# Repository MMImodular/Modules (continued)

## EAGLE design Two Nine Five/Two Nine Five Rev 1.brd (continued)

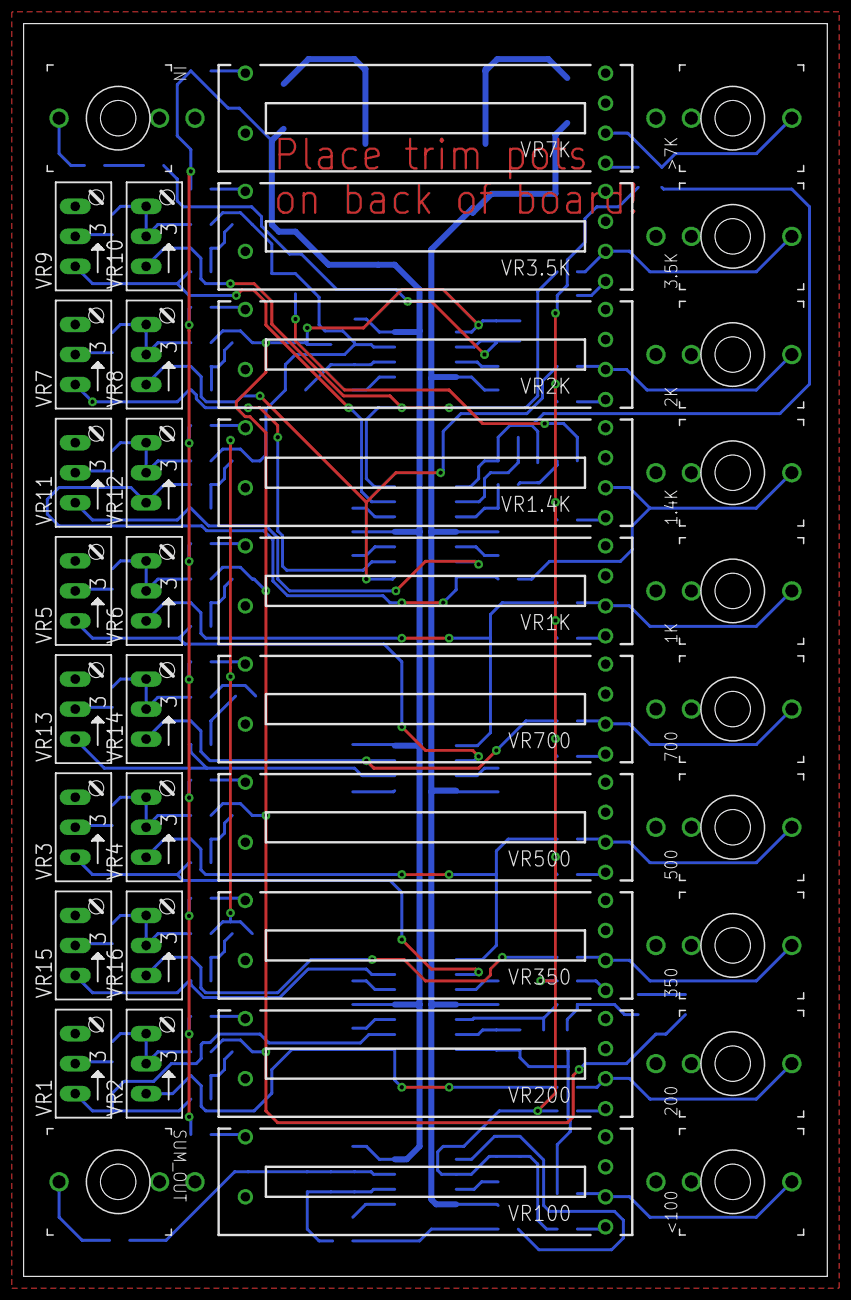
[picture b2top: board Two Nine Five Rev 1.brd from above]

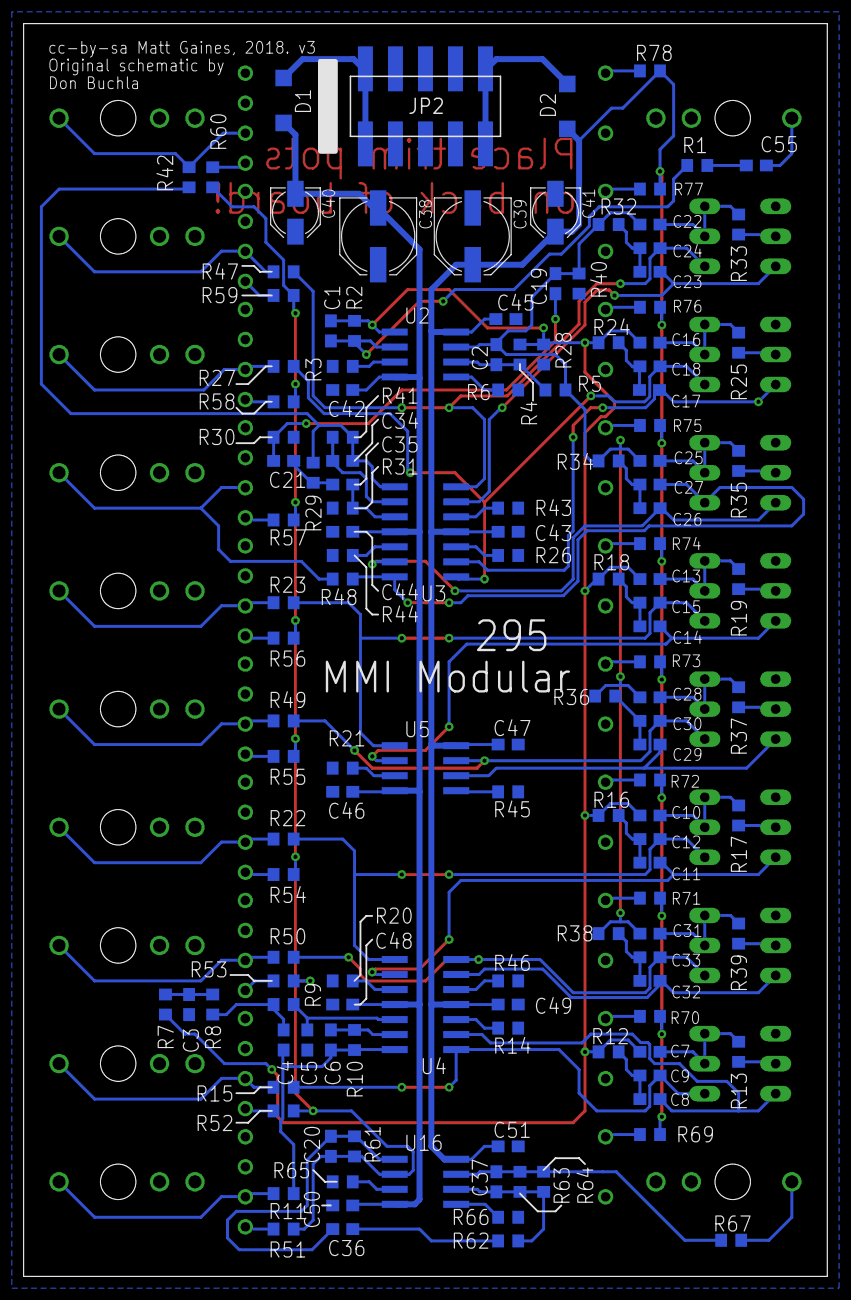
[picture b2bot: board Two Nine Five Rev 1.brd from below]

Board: 2 copper layers, 68.0 x 106.0 mm, 175 parts (137 on the bottom side), 109 nets.

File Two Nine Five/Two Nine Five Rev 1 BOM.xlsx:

Qty | Value | Device | Package | Parts | Description | SPICEPREFIX | Column1
1 |  | PINHD-2X5SMT | 2X05_SMT | JP2 | Surface mount pin header
2 | .0015uF | C-USC0603 | C0603 | C5, C29 | CAPACITOR, American symbol
6 | .0022uF | C-USC0603 | C0603 | C11, C19, C21, C22, C24, C35 | CAPACITOR, American symbol
5 | .0047uF | C-USC0603 | C0603 | C16, C18, C25, C27, C32 | CAPACITOR, American symbol
5 | .01uF | C-USC0603 | C0603 | C8, C13, C15, C28, C30 | CAPACITOR, American symbol
4 | .022uF | C-USC0603 | C0603 | C10, C12, C31, C33 | CAPACITOR, American symbol
3 | .047uF | C-USC0603 | C0603 | C3, C7, C9 | CAPACITOR, American symbol
1 | .22uF | C-USC0603 | C0603 | C4 | CAPACITOR, American symbol
1 | .47uF | C-USC0603 | C0603 | C55 | CAPACITOR, American symbol
1 | 0.47uF | C-USC0603 | C0603 | C36 | CAPACITOR, American symbol
1 | 1.5k | R-US_R0603 | R0603 | R29 | RESISTOR, American symbol
2 | 100k | R-US_R0603 | R0603 | R14, R43 | RESISTOR, American symbol
8 | 100k | TRIM_US-RJ9W | RJ9W | VR1, VR3, VR5, VR7, VR9, VR11, VR13, VR15 | 25-TURN TRIM POTENTIOMETER
10 | 100nF | C-USC0603 | C0603 | C42, C43, C44, C45, C46, C47, C48, C49, C50, C51 | CAPACITOR, American symbol
6 | 100pF | C-USC0603 | C0603 | C1, C2, C6, C20, C34, C37 | CAPACITOR, American symbol
10 | 10k | R-US_R0603 | R0603 | R69, R70, R71, R72, R73, R74, R75, R76, R77, R78 | RESISTOR, American symbol
2 | 10uF | CPOL-USB | PANASONIC_B | C40, C41 | POLARIZED CAPACITOR, American symbol | C
7 | 150k | R-US_R0603 | R0603 | R10, R19, R20, R25, R35, R37, R46 | RESISTOR, American symbol
9 | 15k | R-US_R0603 | R0603 | R6, R12, R16, R18, R24, R32, R34, R36, R38 | RESISTOR, American symbol
5 | 180k | R-US_R0603 | R0603 | R21, R26, R41, R44, R45 | RESISTOR, American symbol
2 | 1N5819 | DIODE-SOD123 | SOD123 | D1, D2 | DIODE
8 | 20k | TRIM_US-RJ9W | RJ9W | VR2, VR4, VR6, VR8, VR10, VR12, VR14, VR16 | POTENTIOMETER
11 | 220 | R-US_R0603 | R0603 | R11, R15, R22, R23, R27, R42, R47, R48, R49, R50, R67 | RESISTOR, American symbol
1 | 220k | R-US_R0603 | R0603 | R31 | RESISTOR, American symbol
2 | 330 | R-US_R0603 | R0603 | R28, R40 | RESISTOR, American symbol
16 | 33k | R-US_R0603 | R0603 | R1, R2, R3, R4, R5, R51, R53, R54, R55, R56, R57, R59, R60, R62, R63, R66 | RESISTOR, American symbol
2 | 39k | R-US_R0603 | R0603 | R52, R58 | RESISTOR, American symbol
1 | 4.7k | R-US_R0603 | R0603 | R65 | RESISTOR, American symbol
2 | 470pF | C-USC0603 | C0603 | C17, C23 | CAPACITOR, American symbol
2 | 47uF | CPOL-USD | PANASONIC_D | C38, C39 | POLARIZED CAPACITOR, American symbol | C
4 | 56k | R-US_R0603 | R0603 | R7, R8, R9, R61 | RESISTOR, American symbol
1 | 6.8k | R-US_R0603 | R0603 | R30 | RESISTOR, American symbol
1 | 65k | R-US_R0603 | R0603 | R64 | RESISTOR, American symbol
2 | 68k | R-US_R0603 | R0603 | R13, R33 | RESISTOR, American symbol
2 | 910pF | C-USC0603 | C0603 | C14, C26 | CAPACITOR, American symbol
2 | 91k | R-US_R0603 | R0603 | R17, R39 | RESISTOR, American symbol
12 | THONKICONNNEW | THONKICONNNEW | WQP-PJ301M-12_JACK | 1.4K, 1K, 2K, 3.5K, 200, 350, 500, 700, <100, >7K, IN, SUM_OUT | 3.5mm socket for Eurorack modular synths
3 | TL072 | TL072_SMD | SO08 | U2, U5, U16 | Generic Dual Op Amp
2 | TL074 | TL074_SMD | SO14 | U3, U4 | Generic Quad Op Amp
10 | 50k (audio or linear) | ALPHA_20MM_ILLUM_FADER | ALPHA_ILL_FADER_20MM_REV2 | VR1.4K, VR1K, VR2K, VR3.5K, VR7K, VR100, VR200, VR350, VR500, VR700 | 20mm Alpha Illuminated Fader

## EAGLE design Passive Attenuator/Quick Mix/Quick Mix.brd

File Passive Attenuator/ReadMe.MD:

# Passive Attenuators
Here are two versions of my passive attenuation module, both have very similar functionality. 

Quick Fix Mix is my first revision, with 5 potentiometers and SMD on the front.

Quick Mix is my second revision, with 6 potentiometers (the 6th controls the level of the mix output) and SMD on the back.

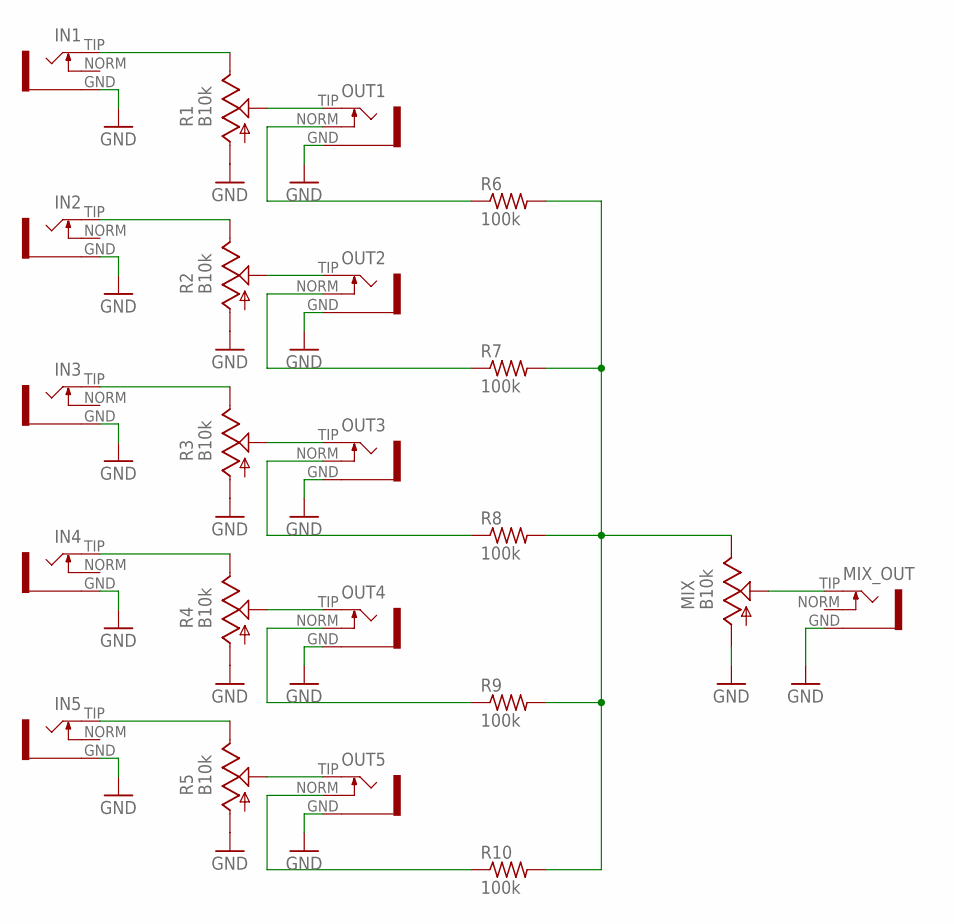
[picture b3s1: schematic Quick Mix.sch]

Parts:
IN1, IN2, IN3, IN4, IN5: INSTRUO_S_JACK_SMALL2
MIX: B10k; OG-POTS_ALPS_POT_VERTICAL
MIX_OUT: INSTRUO_S_JACK_SMALL2
OUT1, OUT2, OUT3, OUT4, OUT5: INSTRUO_S_JACK_S2_INV
R1, R2, R3, R4, R5: B10k; OG-POTS_ALPS_POT_VERTICAL
R6, R7, R8, R9, R10: 100k; R0603

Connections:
GND: IN1.GND, IN2.GND, IN3.GND, IN4.GND, IN5.GND, MIX.P$3 (A), MIX_OUT.GND, OUT1.GND, OUT2.GND, OUT3.GND, OUT4.GND, OUT5.GND, R1.P$3 (A), R2.P$3 (A), R3.P$3 (A), R4.P$3 (A), R5.P$3 (A)
unnamed: IN1.TIP, R1.P$1 (E)
unnamed: OUT4.TIP, R4.P$2 (S)
unnamed: IN2.TIP, R2.P$1 (E)
unnamed: OUT3.TIP, R3.P$2 (S)
unnamed: IN3.TIP, R3.P$1 (E)
unnamed: OUT2.TIP, R2.P$2 (S)
unnamed: IN4.TIP, R4.P$1 (E)
unnamed: OUT1.TIP, R1.P$2 (S)
unnamed: IN5.TIP, R5.P$1 (E)
unnamed: OUT5.TIP, R5.P$2 (S)
unnamed: OUT1.NORM, R6.1
unnamed: OUT2.NORM, R7.1
unnamed: OUT3.NORM, R8.1
unnamed: OUT4.NORM, R9.1
unnamed: OUT5.NORM, R10.1
unnamed: MIX.P$1 (E), R6.2, R7.2, R8.2, R9.2, R10.2
unnamed: MIX.P$2 (S), MIX_OUT.TIP

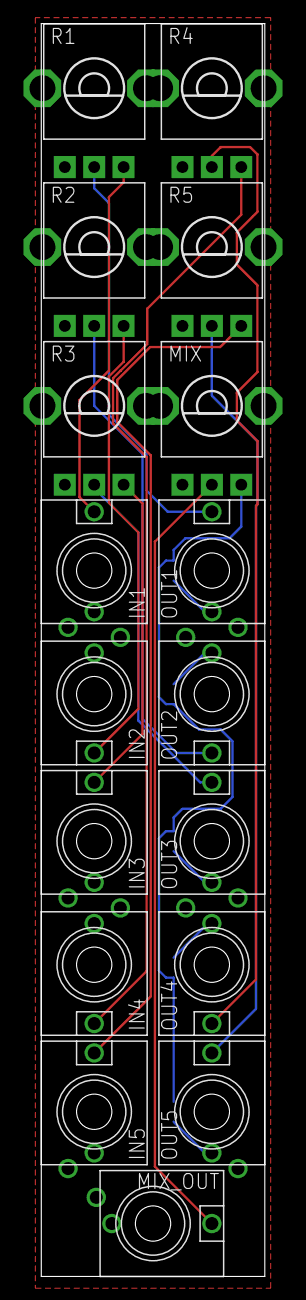
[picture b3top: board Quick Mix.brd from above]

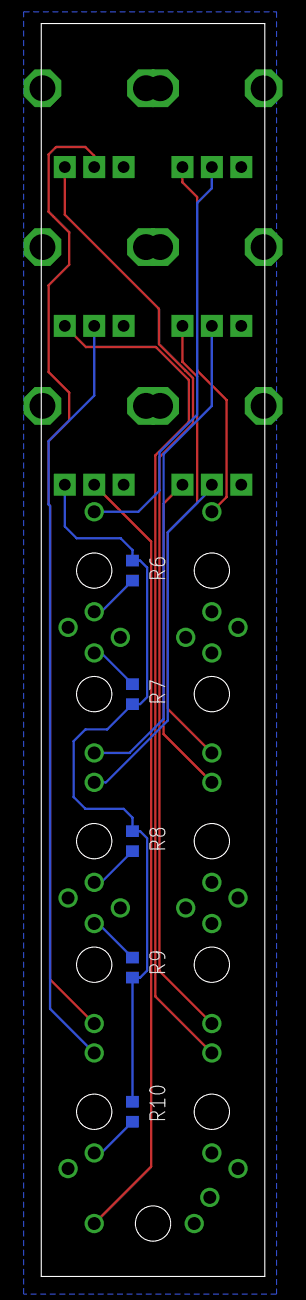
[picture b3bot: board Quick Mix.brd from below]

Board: 2 copper layers, 19.0 x 106.5 mm, 22 parts (5 on the bottom side), 18 nets.

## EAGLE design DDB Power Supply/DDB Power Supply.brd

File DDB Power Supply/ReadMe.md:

# DDB Power Supply
* Utilizes two center-positive isolated DC power bricks to provide Eurorack standard power
* Low-cost design and chainable busboards allow for easy expansion
* +5V regulators per board
* Screw terminals for chaining boards in a system

I created this power supply after building a Trogotronic M15 system. It is based on the same idea of chaining two 12V DC bricks in series to provide bipolar 12V and regulating the +12V rail to provide +5V as necessary.
I disliked the layout of the M15 system and figured I would correct my gripes in this design. It may not be perfect, but if you want perfect, you'd probably be using a linear supply.
These boards can act as bus boards for other supplies. Just connect +/-12V and ground to the proper headers on one of the screw terminals and you're good to go.

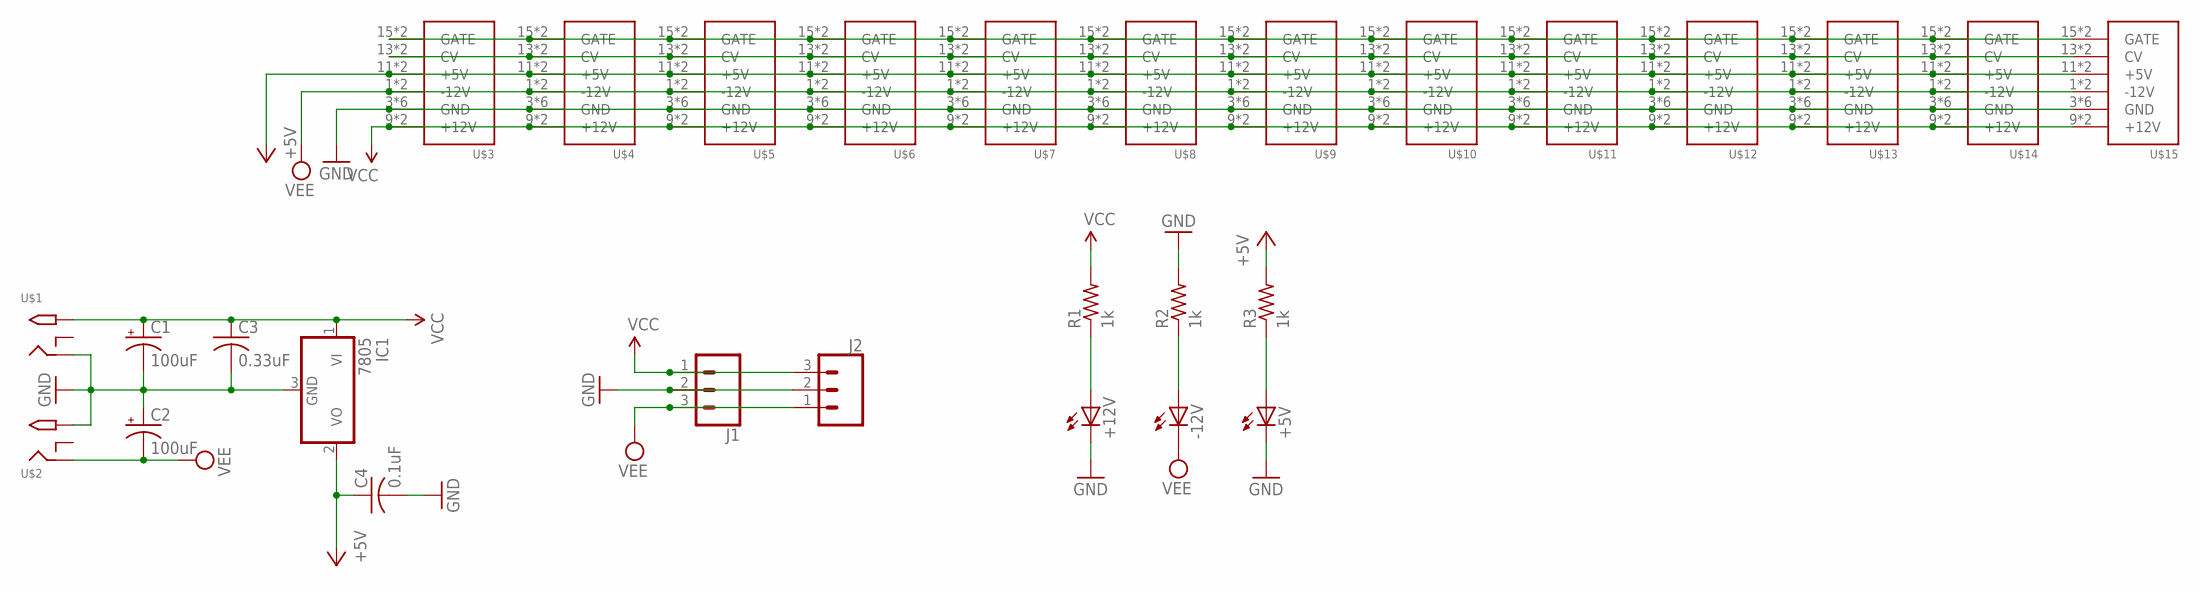
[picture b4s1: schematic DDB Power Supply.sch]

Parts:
+5V, +12V: LED3MM
-12V: LED3MM
C1, C2: 100uF; E3,5-8
C3: 0.33uF; C0805
C4: 0.1uF; C0805
IC1: 7805; TO252
J1, J2: CONN_03SCREW; SCREWTERMINAL-3.5MM-3
R1, R2, R3: 1k; R0805
U$1, U$2: 2.1MMJACKTHM; PJ-102A
U$3, U$4, U$5, U$6, U$7, U$8, U$9, U$10, U$11, U$12, U$13, U$14, U$15: POWER; POWER_16

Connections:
+5V: C4.1, IC1.2 (VO), R3.2, U$3.11 (+5V), U$3.12 (+5V), U$4.11 (+5V), U$4.12 (+5V), U$5.11 (+5V), U$5.12 (+5V), U$6.11 (+5V), U$6.12 (+5V), U$7.11 (+5V), U$7.12 (+5V), U$8.11 (+5V), U$8.12 (+5V), U$9.11 (+5V), U$9.12 (+5V), U$10.11 (+5V), U$10.12 (+5V), U$11.11 (+5V), U$11.12 (+5V), U$12.11 (+5V), U$12.12 (+5V), U$13.11 (+5V), U$13.12 (+5V), U$14.11 (+5V), U$14.12 (+5V), U$15.11 (+5V), U$15.12 (+5V)
GND: +5V.K (C), +12V.K (C), C1.-, C2.+, C3.2, C4.2, IC1.3 (GND), J1.2, J2.2, R2.2, U$1.RING, U$2.TIP, U$3.3 (GND), U$3.4 (GND), U$3.5 (GND), U$3.6 (GND), U$3.7 (GND), U$3.8 (GND), U$4.3 (GND), U$4.4 (GND), U$4.5 (GND), U$4.6 (GND), U$4.7 (GND), U$4.8 (GND), U$5.3 (GND), U$5.4 (GND), U$5.5 (GND), U$5.6 (GND), U$5.7 (GND), U$5.8 (GND), U$6.3 (GND), U$6.4 (GND), U$6.5 (GND), U$6.6 (GND), U$6.7 (GND), U$6.8 (GND), U$7.3 (GND), U$7.4 (GND), U$7.5 (GND), U$7.6 (GND), U$7.7 (GND), U$7.8 (GND), U$8.3 (GND), U$8.4 (GND), U$8.5 (GND), U$8.6 (GND), U$8.7 (GND), U$8.8 (GND), U$9.3 (GND), U$9.4 (GND), U$9.5 (GND), U$9.6 (GND), U$9.7 (GND), U$9.8 (GND), U$10.3 (GND), U$10.4 (GND), U$10.5 (GND), U$10.6 (GND), U$10.7 (GND), U$10.8 (GND), U$11.3 (GND), U$11.4 (GND), U$11.5 (GND), U$11.6 (GND), U$11.7 (GND), U$11.8 (GND), U$12.3 (GND), U$12.4 (GND), U$12.5 (GND), U$12.6 (GND), U$12.7 (GND), U$12.8 (GND), U$13.3 (GND), U$13.4 (GND), U$13.5 (GND), U$13.6 (GND), U$13.7 (GND), U$13.8 (GND), U$14.3 (GND), U$14.4 (GND), U$14.5 (GND), U$14.6 (GND), U$14.7 (GND), U$14.8 (GND), U$15.3 (GND), U$15.4 (GND), U$15.5 (GND), U$15.6 (GND), U$15.7 (GND), U$15.8 (GND)
unnamed: U$3.15 (GATE), U$3.16 (GATE), U$4.15 (GATE), U$4.16 (GATE), U$5.15 (GATE), U$5.16 (GATE), U$6.15 (GATE), U$6.16 (GATE), U$7.15 (GATE), U$7.16 (GATE), U$8.15 (GATE), U$8.16 (GATE), U$9.15 (GATE), U$9.16 (GATE), U$10.15 (GATE), U$10.16 (GATE), U$11.15 (GATE), U$11.16 (GATE), U$12.15 (GATE), U$12.16 (GATE), U$13.15 (GATE), U$13.16 (GATE), U$14.15 (GATE), U$14.16 (GATE), U$15.15 (GATE), U$15.16 (GATE)
unnamed: U$3.13 (CV), U$3.14 (CV), U$4.13 (CV), U$4.14 (CV), U$5.13 (CV), U$5.14 (CV), U$6.13 (CV), U$6.14 (CV), U$7.13 (CV), U$7.14 (CV), U$8.13 (CV), U$8.14 (CV), U$9.13 (CV), U$9.14 (CV), U$10.13 (CV), U$10.14 (CV), U$11.13 (CV), U$11.14 (CV), U$12.13 (CV), U$12.14 (CV), U$13.13 (CV), U$13.14 (CV), U$14.13 (CV), U$14.14 (CV), U$15.13 (CV), U$15.14 (CV)
unnamed: +5V.A, R3.1
unnamed: -12V.A, R2.1
unnamed: +12V.A, R1.1
VCC: C1.+, C3.1, IC1.1 (VI), J1.1, J2.3, R1.2, U$1.TIP, U$3.9 (+12V), U$3.10 (+12V), U$4.9 (+12V), U$4.10 (+12V), U$5.9 (+12V), U$5.10 (+12V), U$6.9 (+12V), U$6.10 (+12V), U$7.9 (+12V), U$7.10 (+12V), U$8.9 (+12V), U$8.10 (+12V), U$9.9 (+12V), U$9.10 (+12V), U$10.9 (+12V), U$10.10 (+12V), U$11.9 (+12V), U$11.10 (+12V), U$12.9 (+12V), U$12.10 (+12V), U$13.9 (+12V), U$13.10 (+12V), U$14.9 (+12V), U$14.10 (+12V), U$15.9 (+12V), U$15.10 (+12V)
VEE: -12V.K (C), C2.-, J1.3, J2.1, U$2.RING, U$3.1 (-12V), U$3.2 (-12V), U$4.1 (-12V), U$4.2 (-12V), U$5.1 (-12V), U$5.2 (-12V), U$6.1 (-12V), U$6.2 (-12V), U$7.1 (-12V), U$7.2 (-12V), U$8.1 (-12V), U$8.2 (-12V), U$9.1 (-12V), U$9.2 (-12V), U$10.1 (-12V), U$10.2 (-12V), U$11.1 (-12V), U$11.2 (-12V), U$12.1 (-12V), U$12.2 (-12V), U$13.1 (-12V), U$13.2 (-12V), U$14.1 (-12V), U$14.2 (-12V), U$15.1 (-12V), U$15.2 (-12V)

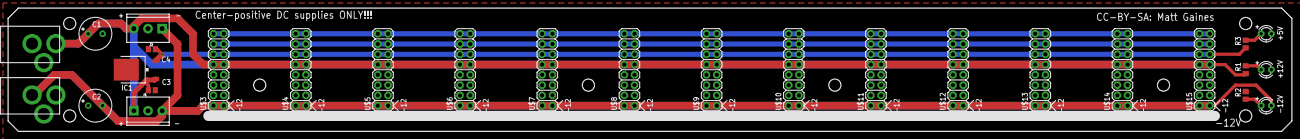
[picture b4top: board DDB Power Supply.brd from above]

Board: 2 copper layers, 317.5 x 30.5 mm, 28 parts (0 on the bottom side), 9 nets.

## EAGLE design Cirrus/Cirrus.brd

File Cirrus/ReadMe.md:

# Cirrus
* Replaced plastic gain potentiometer with dual gang Alpha style potentiometer. These can be found [here](https://www.thonk.co.uk/shop/alpha-9mm-pots-dshaft/)
* Changed all 10uF capacitors to the Panasonic B footprint. Dimensions can be found [here](https://www.mouser.com/datasheet/2/315/ABA0000C1251-1138508.pdf)
* Moved some capacitors around to make hand soldering easier

Cirrus is my rework of the popular Clouds module, originally designed by Émilie Gillet of Mutable Instruments. After building several Clouds myself, I found several problems that were easy to fix with a simple PCB revision. I decided it would be worth the effort, so here it is.

PCBs can be purchased through [Pusherman](https://pushermanproductions.com/product/claude-texture-synthesizer-pcb/)

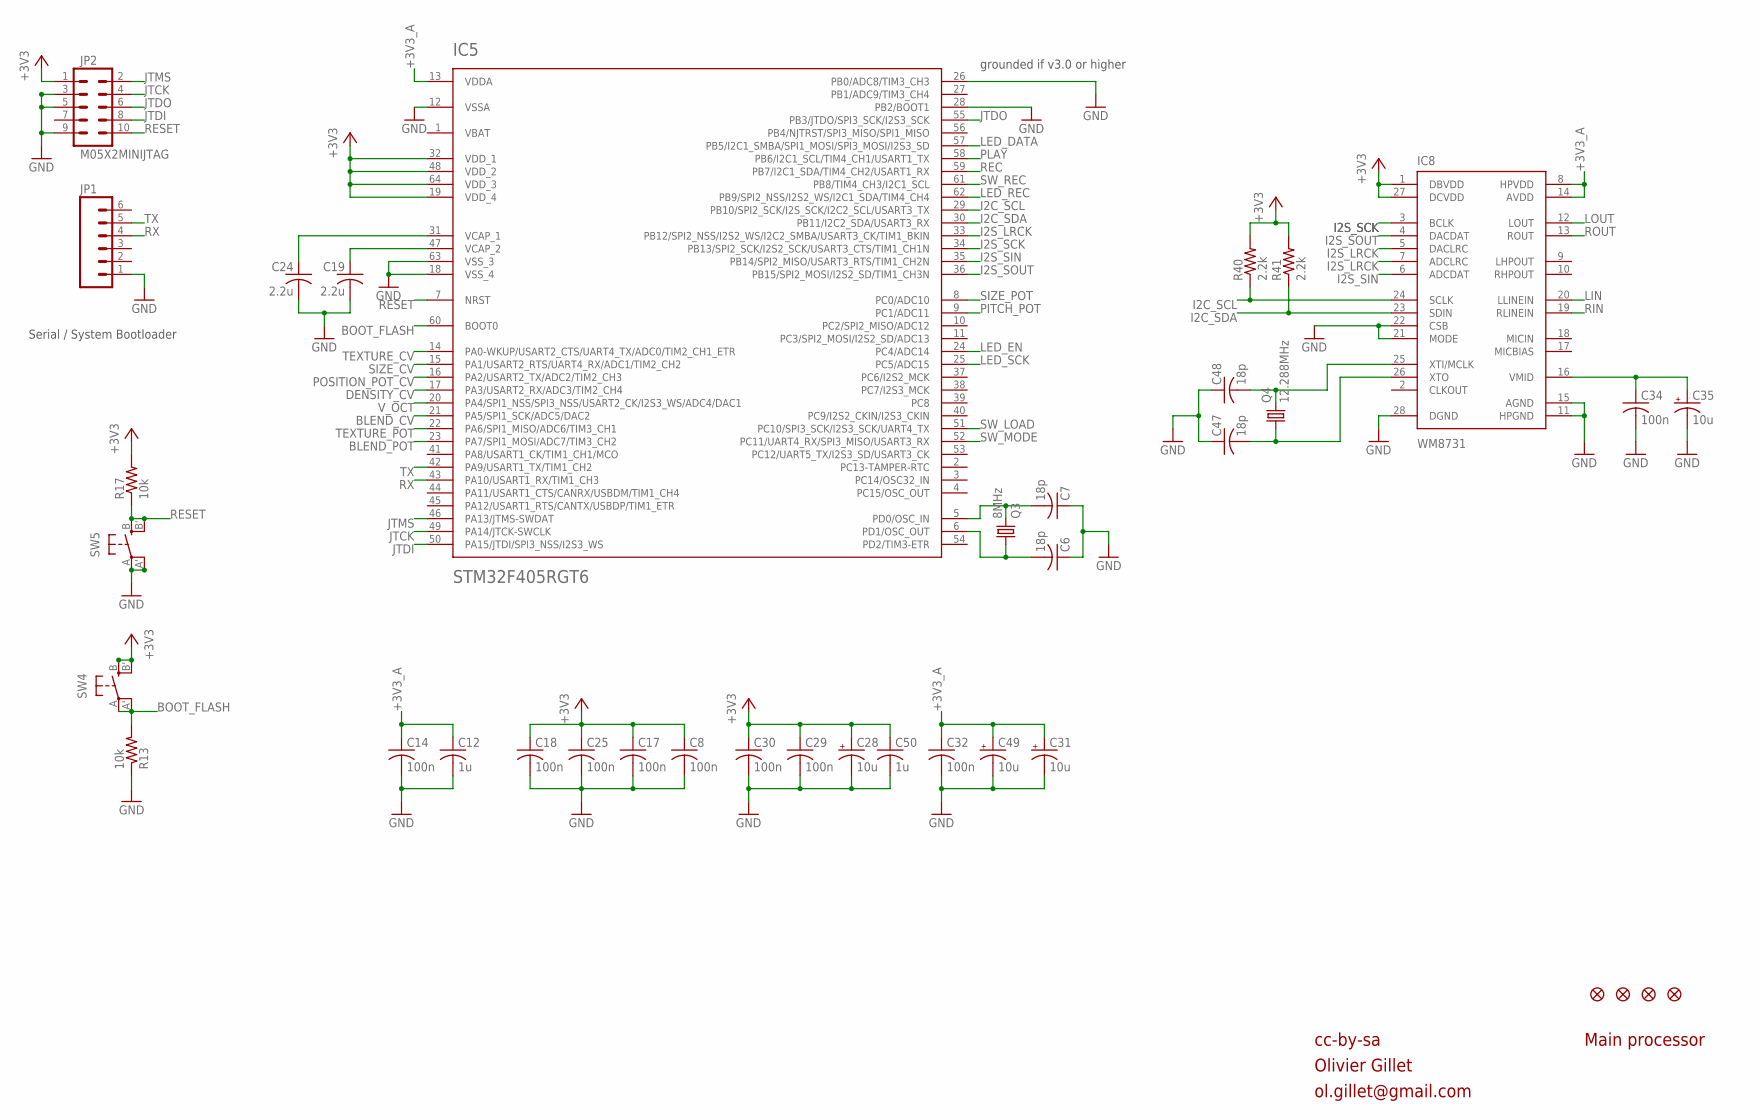
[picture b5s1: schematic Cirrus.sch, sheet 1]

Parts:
C6, C7, C47, C48: 18p; C0603
C8, C14, C17, C18, C25, C29, C30, C32, C34: 100n; C0603
C12, C50: 1u; C0603
C19, C24: 2.2u; C0805
C28, C31, C35, C49: 10u; PANASONIC_B
F1, F2, F3, F4: FIDUCIAL1X2; FIDUCIAL-1X2
IC5: STM32F405RGT6; TQFP-10X10-64
IC8: WM8731; SSOP28
JP1: M06SIP; 1X06
JP2: M05X2MINIJTAG; 2X5-1.27
Q3: 8MHz; HC49UP
Q4: 12.288MHz; HC49UP
R13, R17: 10k; R0603
R40, R41: 2.2k; R0603
SW4, SW5: EVQQ2; EVQ-Q2

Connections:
+3V3: C8.1, C17.1, C18.1, C25.1, C28.+, C29.1, C30.1, C50.1, IC5.19 (VDD_4), IC5.32 (VDD_1), IC5.48 (VDD_2), IC5.64 (VDD_3), IC8.1 (DBVDD), IC8.27 (DCVDD), JP2.1, R17.2, R40.2, R41.2, SW4.B (S), SW4.B' (S1); also elsewhere on the board
+3V3_A: C12.1, C14.1, C31.+, C32.1, C49.+, IC5.13 (VDDA), IC8.8 (HPVDD), IC8.14 (AVDD); also elsewhere on the board
BLEND_CV: IC5.21 (PA5/SPI1_SCK/ADC5/DAC2); also elsewhere on the board
BLEND_POT: IC5.23 (PA7/SPI1_MOSI/ADC7/TIM3_CH2); also elsewhere on the board
BOOT_FLASH: IC5.60 (BOOT0), R13.2, SW4.A, SW4.A' (P1)
DENSITY_CV: IC5.17 (PA3/USART2_RX/ADC3/TIM2_CH4); also elsewhere on the board
GND: C6.1, C7.1, C8.2, C12.2, C14.2, C17.2, C18.2, C19.2, C24.2, C25.2, C28.-, C29.2, C30.2, C31.-, C32.2, C34.2, C35.-, C47.1, C48.1, C49.-, C50.2, IC5.12 (VSSA), IC5.18 (VSS_4), IC5.26 (PB0/ADC8/TIM3_CH3), IC5.28 (PB2/BOOT1), IC5.63 (VSS_3), IC8.11 (HPGND), IC8.15 (AGND), IC8.21 (MODE), IC8.22 (CSB), IC8.28 (DGND), JP1.1, JP2.3, JP2.5, JP2.9, R13.1, SW5.A, SW5.A' (P1); also elsewhere on the board
I2C_SCL: IC5.29 (PB10/SPI2_SCK/I2S_SCK/I2C2_SCL/USART3_TX), IC8.24 (SCLK), R40.1
I2C_SDA: IC5.30 (PB11/I2C2_SDA/USART3_RX), IC8.23 (SDIN), R41.1
I2S_LRCK: IC5.33 (PB12/SPI2_NSS/I2S2_WS/I2C2_SMBA/USART3_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), IC8.5 (DACLRC), IC8.7 (ADCLRC)
I2S_SCK: IC5.34 (PB13/SPI2_SCK/I2S2_SCK/USART3_CTS/TIM1_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), IC8.3 (BCLK)
I2S_SIN: IC5.35 (PB14/SPI2_MISO/USART3_RTS/TIM1_CH2N), IC8.6 (ADCDAT)
I2S_SOUT: IC5.36 (PB15/SPI2_MOSI/I2S2_SD/TIM1_CH3N), IC8.4 (DACDAT)
JTCK: IC5.49 (PA14/JTCK-SWCLK), JP2.4
JTDI: IC5.50 (PA15/JTDI/SPI3_NSS/I2S3_WS), JP2.8
JTDO: IC5.55 (PB3/JTDO/SPI3_SCK/I2S3_SCK), JP2.6
JTMS: IC5.46 (PA13/JTMS-SWDAT), JP2.2
LED_DATA: IC5.57 (PB5/I2C1_SMBA/SPI1_MOSI/SPI3_MOSI/I2S3_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); also elsewhere on the board
LED_EN: IC5.24 (PC4/ADC14); also elsewhere on the board
LED_REC: IC5.62 (PB9/SPI2_NSS/I2S2_WS/I2C1_SDA/TIM4_CH4); also elsewhere on the board
LED_SCK: IC5.25 (PC5/ADC15); also elsewhere on the board
LIN: IC8.20 (LLINEIN); also elsewhere on the board
LOUT: IC8.12 (LOUT); also elsewhere on the board
unnamed: C7.2, IC5.5 (PD0/OSC_IN), Q3.2
unnamed: C6.2, IC5.6 (PD1/OSC_OUT), Q3.1
unnamed: C19.1, IC5.47 (VCAP_2)
unnamed: C34.1, C35.+, IC8.16 (VMID)
unnamed: C24.1, IC5.31 (VCAP_1)
unnamed: C47.2, IC8.26 (XTO), Q4.1
unnamed: C48.2, IC8.25 (XTI/MCLK), Q4.2
PITCH_POT: IC5.9 (PC1/ADC11); also elsewhere on the board
PLAY: IC5.58 (PB6/I2C1_SCL/TIM4_CH1/USART1_TX); also elsewhere on the board
POSITION_POT_CV: IC5.16 (PA2/USART2_TX/ADC2/TIM2_CH3); also elsewhere on the board
REC: IC5.59 (PB7/I2C1_SDA/TIM4_CH2/USART1_RX); also elsewhere on the board
RESET: IC5.7 (NRST), JP2.10, R17.1, SW5.B (S), SW5.B' (S1)
RIN: IC8.19 (RLINEIN); also elsewhere on the board
ROUT: IC8.13 (ROUT); also elsewhere on the board
RX: IC5.43 (PA10/USART1_RX/TIM1_CH3), JP1.4
SIZE_CV: IC5.15 (PA1/USART2_RTS/UART4_RX/ADC1/TIM2_CH2); also elsewhere on the board
SIZE_POT: IC5.8 (PC0/ADC10); also elsewhere on the board
SW_LOAD: IC5.51 (PC10/SPI3_SCK/I2S3_SCK/UART4_TX); also elsewhere on the board
SW_MODE: IC5.52 (PC11/UART4_RX/SPI3_MISO/USART3_RX); also elsewhere on the board
SW_REC: IC5.61 (PB8/TIM4_CH3/I2C1_SCL); also elsewhere on the board
TEXTURE_CV: IC5.14 (PA0-WKUP/USART2_CTS/UART4_TX/ADC0/TIM2_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); also elsewhere on the board
TEXTURE_POT: IC5.22 (PA6/SPI1_MISO/ADC6/TIM3_CH1); also elsewhere on the board
TX: IC5.42 (PA9/USART1_TX/TIM1_CH2), JP1.5
VBAT: IC5.1 (VBAT)
V_OCT: IC5.20 (PA4/SPI1_NSS/SPI3_NSS/USART2_CK/I2S3_WS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); also elsewhere on the board

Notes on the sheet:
cc-by-sa
Olivier Gillet
ol.gillet@gmail.com
Main processor
Serial / System Bootloader
grounded if v3.0 or higher

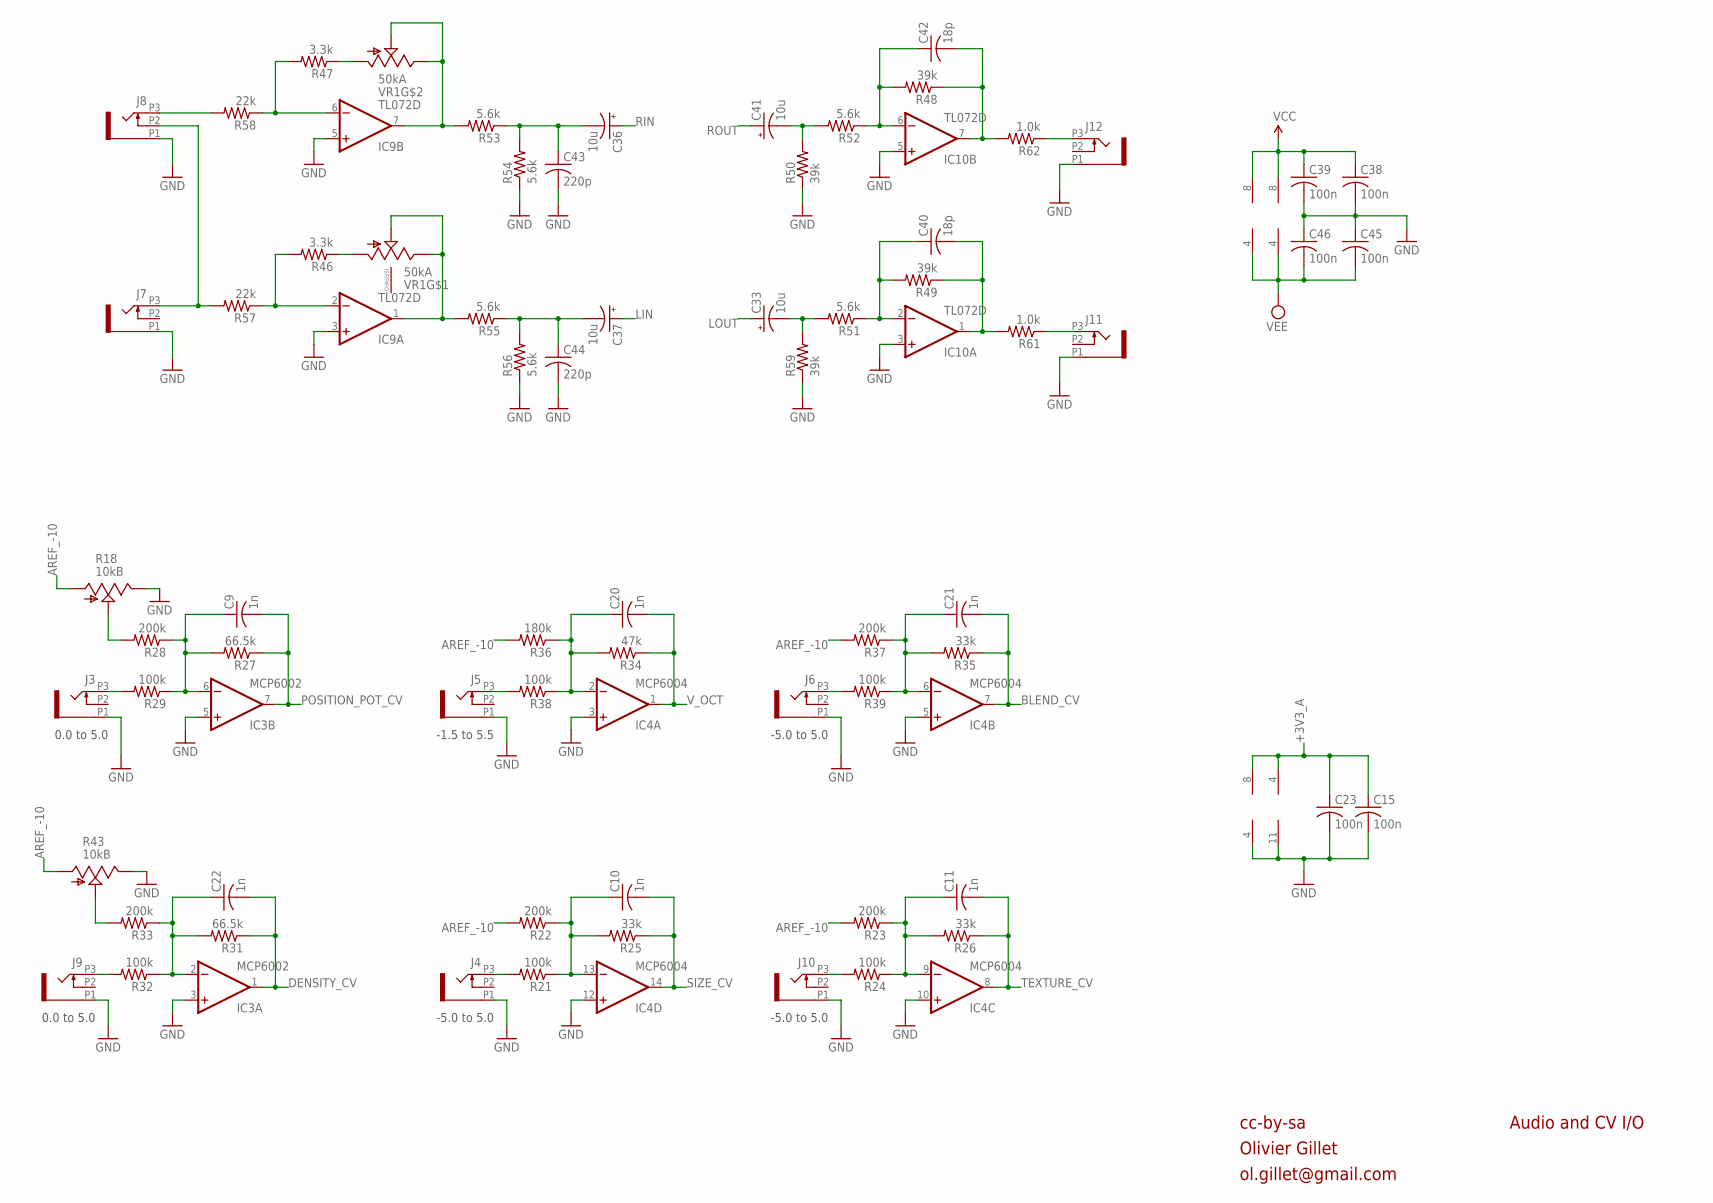
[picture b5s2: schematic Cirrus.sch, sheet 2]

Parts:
C9, C10, C11, C20, C21, C22: 1n; C0603
C15, C23, C38, C39, C45, C46: 100n; C0603
C33, C36, C37, C41: 10u; PANASONIC_B
C40, C42: 18p; C0603
C43, C44: 220p; C0603
IC3: MCP6002; SO08
IC4: MCP6004; SO14
IC9, IC10: TL072D; SO08
J3, J4, J5, J6, J7, J8, J9, J10, J11, J12: PJ301_THONKICONN6; WQP_PJ_301M6
R18, R43: 10kB; ALPS_POT_VERTICAL_PS
R21, R24, R29, R32, R38, R39: 100k; R0603
R22, R23, R28, R33, R37: 200k; R0603
R25, R26, R35: 33k; R0603
R27, R31: 66.5k; R0603
R34: 47k; R0603
R36: 180k; R0603
R46, R47: 3.3k; R0603
R48, R49, R50, R59: 39k; R0603
R51, R52, R53, R54, R55, R56: 5.6k; R0603
R57, R58: 22k; R0603
R61, R62: 1.0k; R0603
VR1: 50kA; DUAL_9MM_SNAP-IN_POT

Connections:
+3V3_A: C15.1, C23.1, IC3.8 (V+), IC4.4 (V+); also elsewhere on the board
AREF_-10: R18.P$3 (A), R22.2, R23.2, R36.2, R37.2, R43.P$3 (A); also elsewhere on the board
BLEND_CV: C21.2, IC4.7 (OUT), R35.1; also elsewhere on the board
DENSITY_CV: C22.2, IC3.1 (OUT), R31.1; also elsewhere on the board
GND: C15.2, C23.2, C38.2, C39.2, C43.2, C44.2, C45.1, C46.1, IC3.3 (+IN), IC3.4 (V-), IC3.5 (+IN), IC4.3 (+IN), IC4.5 (+IN), IC4.10 (+IN), IC4.11 (V-), IC4.12 (+IN), IC9.3 (+IN), IC9.5 (+IN), IC10.3 (+IN), IC10.5 (+IN), J3.P1 (1), J4.P1 (1), J5.P1 (1), J6.P1 (1), J7.P1 (1), J8.P1 (1), J9.P1 (1), J10.P1 (1), J11.P1 (1), J12.P1 (1), R18.P$1 (E), R43.P$1 (E), R50.1, R54.1, R56.1, R59.1; also elsewhere on the board
LIN: C37.+; also elsewhere on the board
LOUT: C33.+; also elsewhere on the board
LOUT_JACK: J11.P3 (3), R61.1
unnamed: J4.P3 (3), R21.2
unnamed: C10.1, IC4.13 (-IN), R21.1, R22.1, R25.2
unnamed: R47.1, VR1.1B (A)
unnamed: J10.P3 (3), R24.2
unnamed: C11.1, IC4.9 (-IN), R23.1, R24.1, R26.2
unnamed: J6.P3 (3), R39.2
unnamed: J5.P3 (3), R38.2
unnamed: C20.1, IC4.2 (-IN), R34.2, R36.1, R38.1
unnamed: J9.P3 (3), R32.2
unnamed: C21.1, IC4.6 (-IN), R35.2, R37.1, R39.1
unnamed: C37.-, C44.1, R55.1, R56.2
unnamed: J8.P3 (3), R58.2
unnamed: J7.P3 (3), J8.P2 (2), R57.2
unnamed: C36.-, C43.1, R53.1, R54.2
unnamed: C41.-, R50.2, R52.2
unnamed: C22.1, IC3.2 (-IN), R31.2, R32.1, R33.1
unnamed: C42.1, IC10.6 (-IN), R48.2, R52.1
unnamed: R33.2, R43.P$2 (S)
unnamed: J3.P3 (3), R29.2
unnamed: C42.2, IC10.7 (OUT), R48.1, R62.2
unnamed: C9.1, IC3.6 (-IN), R27.2, R28.1, R29.1
unnamed: C33.-, R51.2, R59.2
unnamed: C40.1, IC10.2 (-IN), R49.2, R51.1
unnamed: C40.2, IC10.1 (OUT), R49.1, R61.2
unnamed: R18.P$2 (S), R28.2
unnamed: IC9.7 (OUT), R53.2, VR1.2B (S), VR1.3B (E)
unnamed: IC9.1 (OUT), R55.2, VR1.2 (S), VR1.3 (E)
unnamed: R46.1, VR1.1 (A)
unnamed: IC9.6 (-IN), R47.2, R58.1
unnamed: IC9.2 (-IN), R46.2, R57.1
POSITION_POT_CV: C9.2, IC3.7 (OUT), R27.1; also elsewhere on the board
RIN: C36.+; also elsewhere on the board
ROUT: C41.+; also elsewhere on the board
ROUT_JACK: J12.P3 (3), R62.1
SIZE_CV: C10.2, IC4.14 (OUT), R25.1; also elsewhere on the board
TEXTURE_CV: C11.2, IC4.8 (OUT), R26.1; also elsewhere on the board
VCC: C38.1, C39.1, IC9.8 (V+), IC10.8 (V+); also elsewhere on the board
VEE: C45.2, C46.2, IC9.4 (V-), IC10.4 (V-); also elsewhere on the board
V_OCT: C20.2, IC4.1 (OUT), R34.1; also elsewhere on the board

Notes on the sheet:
cc-by-sa
Olivier Gillet
ol.gillet@gmail.com
Audio and CV I/O
0.0 to 5.0
-1.5 to 5.5
-5.0 to 5.0

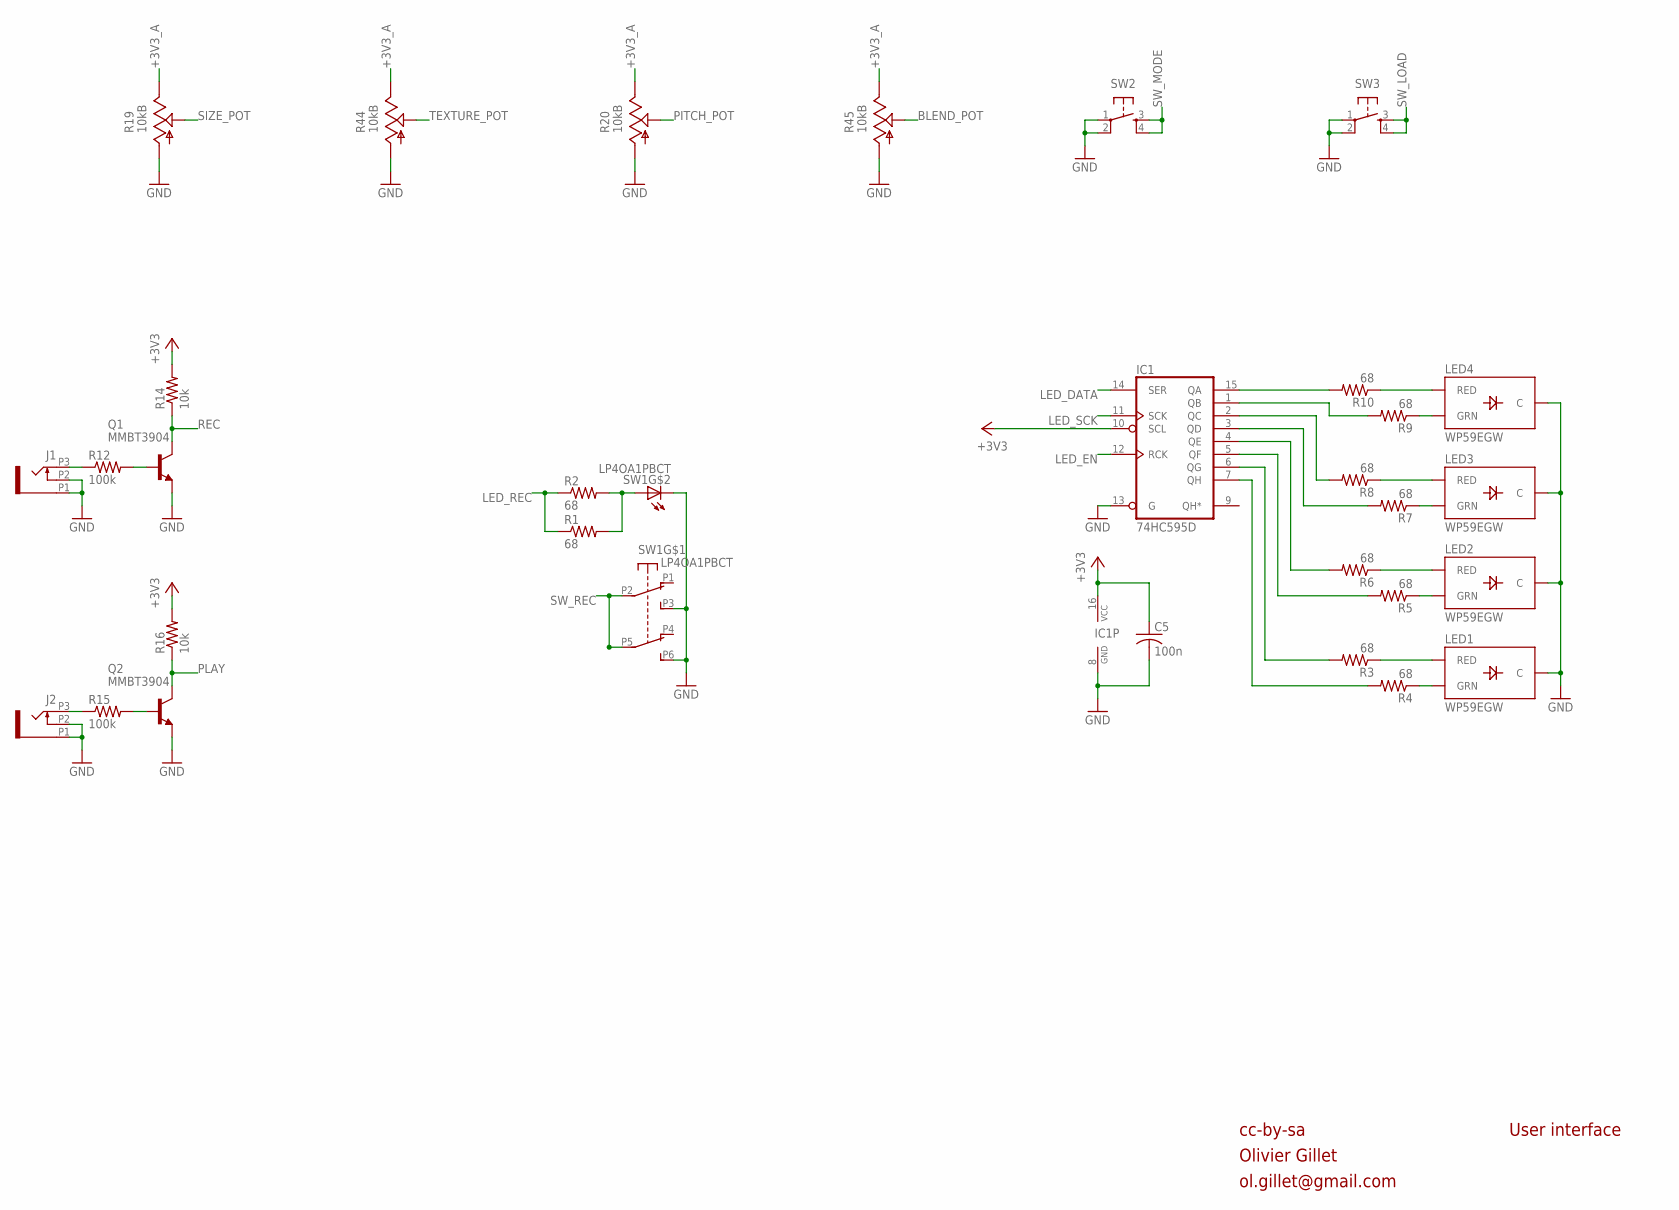
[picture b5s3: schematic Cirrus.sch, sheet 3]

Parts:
C5: 100n; C0603
IC1: 74HC595D; SO16
J1, J2: PJ301_THONKICONN6; WQP_PJ_301M6
LED1, LED2, LED3, LED4: WP59EGW; LED-BICOLOR-THROUGHHOLE-5MM
Q1, Q2: MMBT3904; SOT23-BEC
R1, R2, R3, R4, R5, R6, R7, R8, R9, R10: 68; R0603
R12, R15: 100k; R0603
R14, R16: 10k; R0603
R19, R20, R44, R45: 10kB; ALPS_POT_VERTICAL_PS
SW1: LP4OA1PBCT
SW2, SW3: TAC_SWITCHPTH; TACTILE-PTH

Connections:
+3V3: C5.1, IC1.10 (SCL), IC1.16 (VCC), R14.2, R16.2; also elsewhere on the board
+3V3_A: R19.P$1 (E), R20.P$1 (E), R44.P$1 (E), R45.P$1 (E); also elsewhere on the board
BLEND_POT: R45.P$2 (S); also elsewhere on the board
GND: C5.2, IC1.8 (GND), IC1.13 (G), J1.P1 (1), J1.P2 (2), J2.P1 (1), J2.P2 (2), LED1.2 (C), LED2.2 (C), LED3.2 (C), LED4.2 (C), Q1.E, Q2.E, R19.P$3 (A), R20.P$3 (A), R44.P$3 (A), R45.P$3 (A), SW1.L2, SW1.P3 (A3), SW1.P6 (B3), SW2.1, SW2.2, SW3.1, SW3.2; also elsewhere on the board
LED_DATA: IC1.14 (SER); also elsewhere on the board
LED_EN: IC1.12 (RCK); also elsewhere on the board
LED_REC: R1.1, R2.1; also elsewhere on the board
LED_SCK: IC1.11 (SCK); also elsewhere on the board
unnamed: LED4.3 (GRN), R9.1
unnamed: LED4.1 (RED), R10.1
unnamed: LED3.1 (RED), R8.1
unnamed: LED3.3 (GRN), R7.1
unnamed: LED2.1 (RED), R6.1
unnamed: J2.P3 (3), R15.1
unnamed: Q2.B, R15.2
unnamed: R1.2, R2.2, SW1.L1
unnamed: LED2.3 (GRN), R5.1
unnamed: LED1.1 (RED), R3.1
unnamed: LED1.3 (GRN), R4.1
unnamed: IC1.15 (QA), R10.2
unnamed: IC1.1 (QB), R9.2
unnamed: IC1.2 (QC), R8.2
unnamed: IC1.3 (QD), R7.2
unnamed: IC1.4 (QE), R6.2
unnamed: IC1.5 (QF), R5.2
unnamed: IC1.6 (QG), R3.2
unnamed: IC1.7 (QH), R4.2
unnamed: J1.P3 (3), R12.1
unnamed: Q1.B, R12.2
PITCH_POT: R20.P$2 (S); also elsewhere on the board
PLAY: Q2.C, R16.1; also elsewhere on the board
REC: Q1.C, R14.1; also elsewhere on the board
SIZE_POT: R19.P$2 (S); also elsewhere on the board
SW_LOAD: SW3.3, SW3.4; also elsewhere on the board
SW_MODE: SW2.3, SW2.4; also elsewhere on the board
SW_REC: SW1.P2 (A2), SW1.P5 (B2); also elsewhere on the board
TEXTURE_POT: R44.P$2 (S); also elsewhere on the board

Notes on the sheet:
cc-by-sa
Olivier Gillet
ol.gillet@gmail.com
User interface
